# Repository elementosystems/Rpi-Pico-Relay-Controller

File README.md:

# Rpi-Pico-Relay-Controller
IO control board for remote Lab Environment

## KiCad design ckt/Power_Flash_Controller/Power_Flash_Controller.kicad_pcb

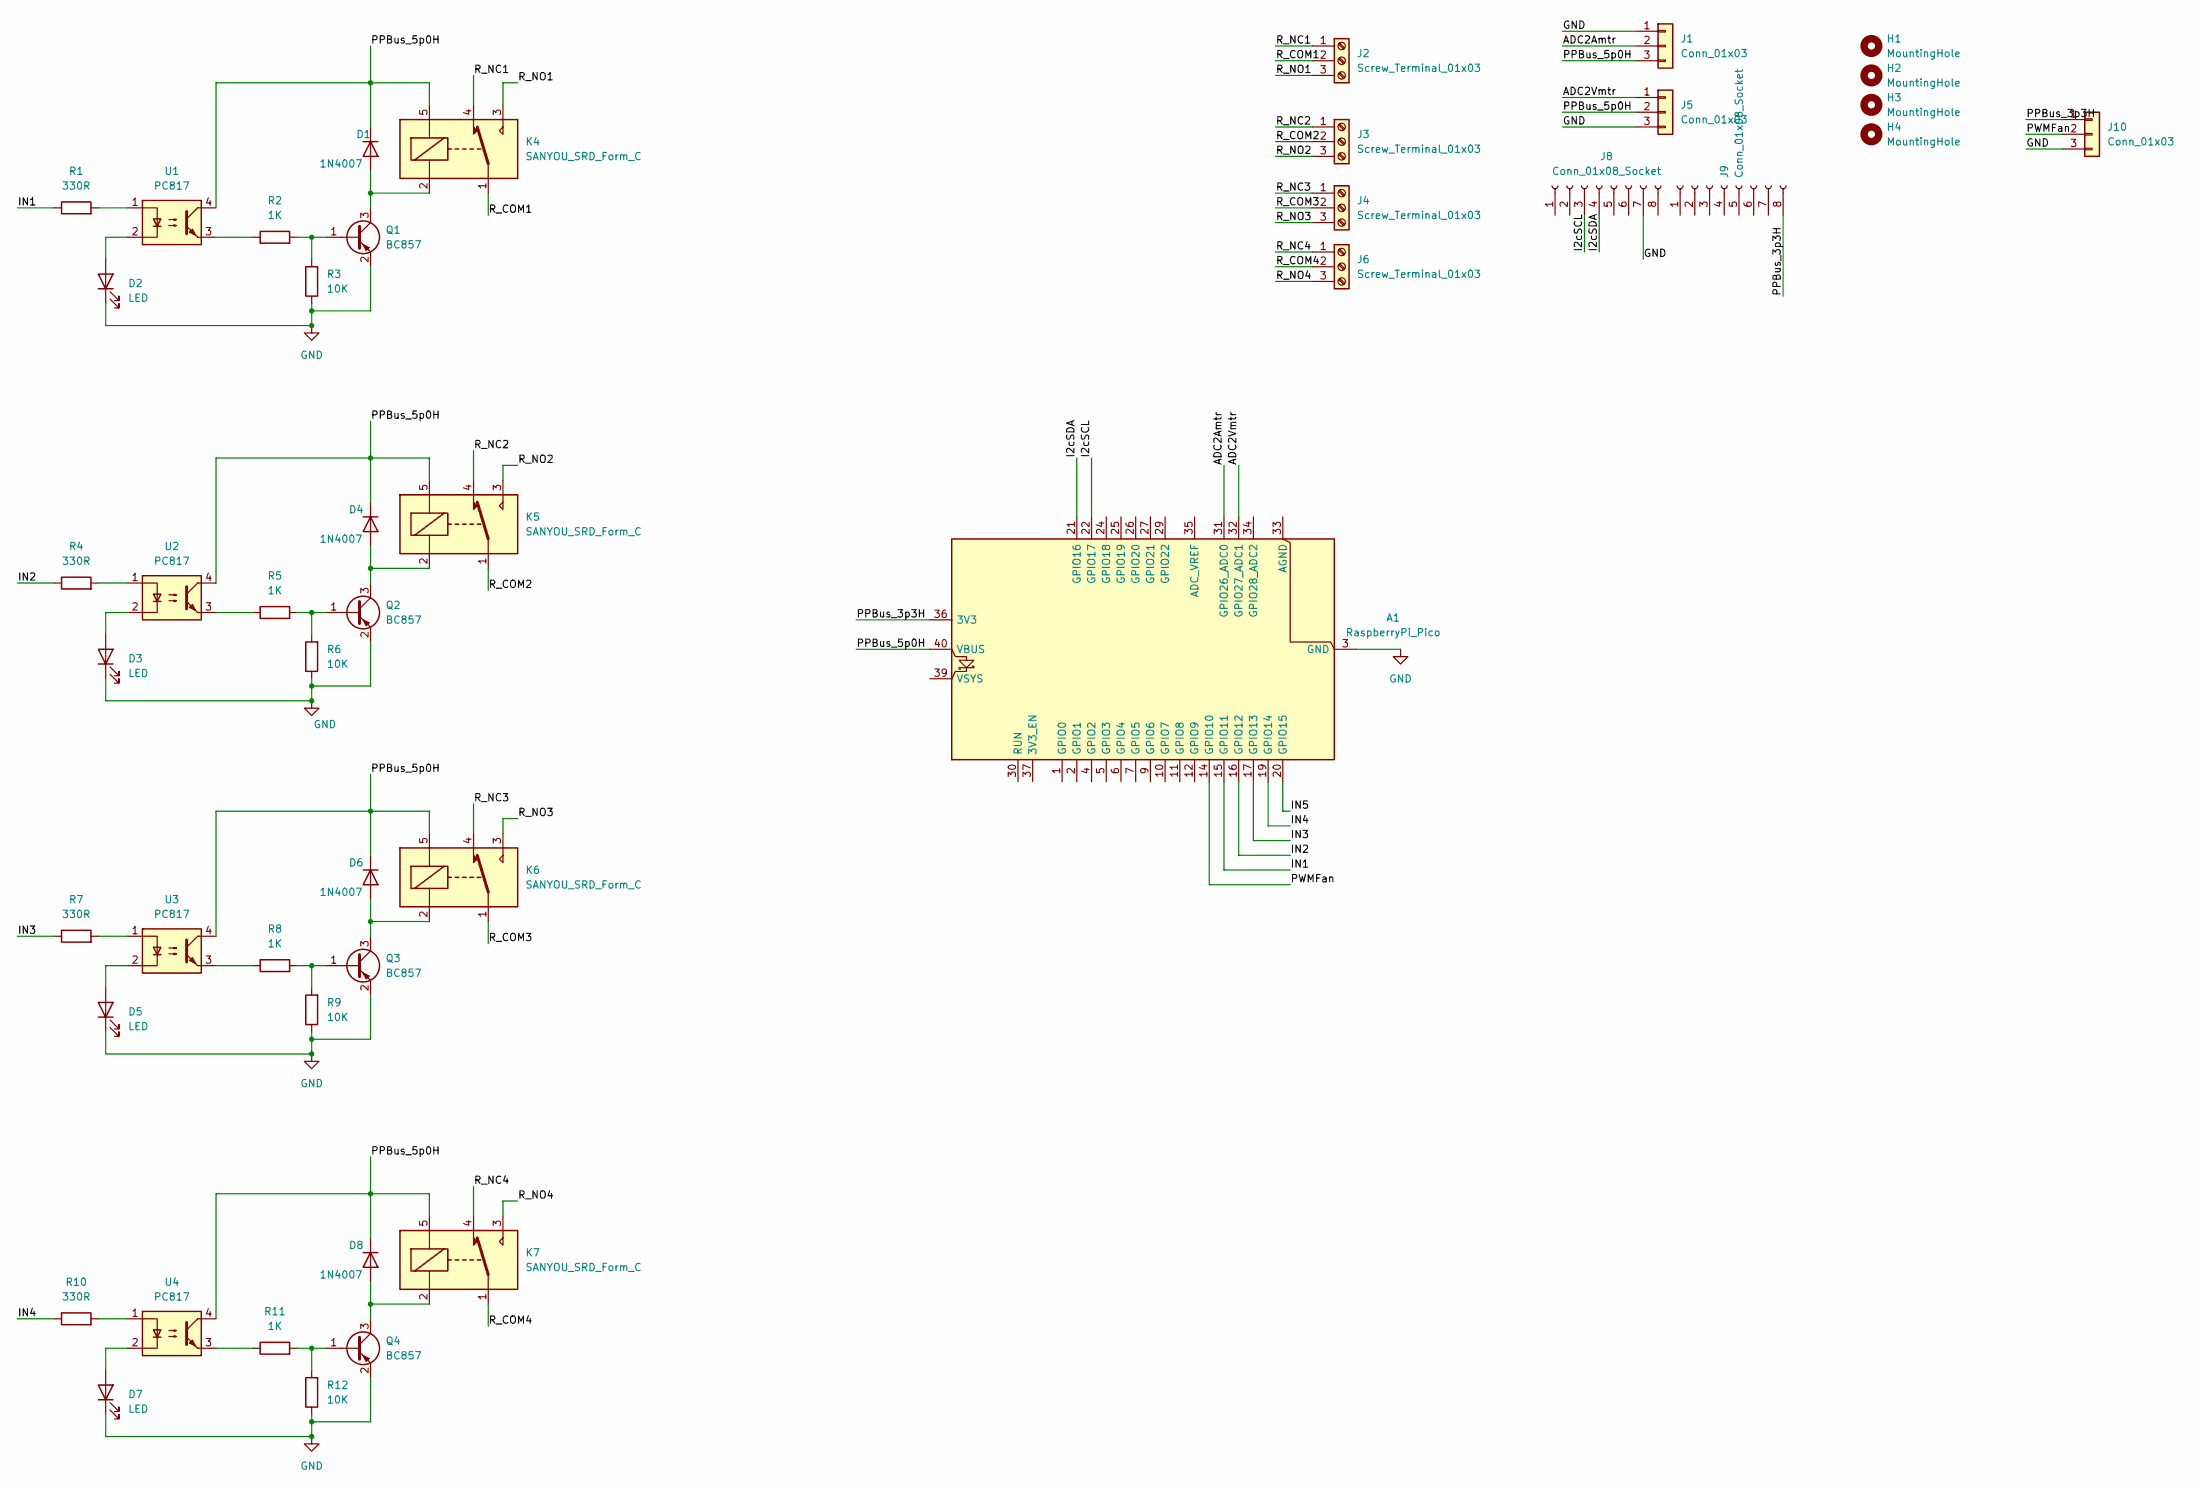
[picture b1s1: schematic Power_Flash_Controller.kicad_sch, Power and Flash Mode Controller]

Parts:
A1: RaspberryPi_Pico; RaspberryPi_Pico_Common_Unspecified
D1, D4, D6, D8: 1N4007; D_DO-41_SOD81_P10.16mm_Horizontal
D2, D3, D5, D7: LED; LED_D3.0mm_IRBlack
H1, H2, H3, H4: MountingHole; MountingHole_2.2mm_M2_DIN965_Pad_TopOnly
J1, J5, J10: Conn_01x03; PinHeader_1x03_P2.54mm_Vertical
J2, J3, J4, J6: Screw_Terminal_01x03; TerminalBlock_MaiXu_MX126-5.0-03P_1x03_P5.00mm
J8, J9: Conn_01x08_Socket; PinHeader_1x08_P2.54mm_Vertical
K4, K5, K6, K7: SANYOU_SRD_Form_C; Relay_SPDT_SANYOU_SRD_Series_Form_C
Q1, Q2, Q3, Q4: BC857; SOT-23
R1, R4, R7, R10: 330R; R_Axial_DIN0204_L3.6mm_D1.6mm_P7.62mm_Horizontal
R2, R5, R8, R11: 1K; R_Axial_DIN0204_L3.6mm_D1.6mm_P7.62mm_Horizontal
R3, R6, R9, R12: 10K; R_Axial_DIN0204_L3.6mm_D1.6mm_P7.62mm_Horizontal
U1, U2, U3, U4: PC817; DIP-4_W7.62mm

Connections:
/ADC2Amtr: A1.31 (GPIO26_ADC0), J1.2
/ADC2Vmtr: A1.32 (GPIO27_ADC1), J5.1
/I2cSCL: A1.22 (GPIO17), J8.3
/I2cSDA: A1.21 (GPIO16), J8.4
/IN1: A1.15 (GPIO11), R1.1
/IN2: A1.16 (GPIO12), R4.1
/IN3: A1.17 (GPIO13), R7.1
/IN4: A1.19 (GPIO14), R10.1
/IN5: A1.20 (GPIO15)
/PPBus_3p3H: A1.36 (3V3), J9.8, J10.1
/PPBus_5p0H: A1.40 (VBUS), D1.1 (K), D4.1 (K), D6.1 (K), D8.1 (K), J1.3, J5.2, K4.5, K5.5, K6.5, K7.5, U1.4, U2.4, U3.4, U4.4
/PWMFan: A1.14 (GPIO10), J10.2
/R_COM1: J2.2, K4.1
/R_COM2: J3.2, K5.1
/R_COM3: J4.2, K6.1
/R_COM4: J6.2, K7.1
/R_NC1: J2.1, K4.4
/R_NC2: J3.1, K5.4
/R_NC3: J4.1, K6.4
/R_NC4: J6.1, K7.4
/R_NO1: J2.3, K4.3
/R_NO2: J3.3, K5.3
/R_NO3: J4.3, K6.3
/R_NO4: J6.3, K7.3
GND: A1.3 (GND), A1.8 (GND), A1.13 (GND), A1.18 (GND), A1.23 (GND), A1.28 (GND), A1.38 (GND), D2.1 (K), D3.1 (K), D5.1 (K), D7.1 (K), J1.1, J5.3, J8.7, J10.3, Q1.2 (E), Q2.2 (E), Q3.2 (E), Q4.2 (E), R3.1, R6.1, R9.1, R12.1
unnamed: D1.2 (A), K4.2, Q1.3 (C)
unnamed: D2.2 (A), U1.2
unnamed: D3.2 (A), U2.2
unnamed: D4.2 (A), K5.2, Q2.3 (C)
unnamed: D5.2 (A), U3.2
unnamed: D6.2 (A), K6.2, Q3.3 (C)
unnamed: D7.2 (A), U4.2
unnamed: D8.2 (A), K7.2, Q4.3 (C)
unnamed: Q1.1 (B), R2.2, R3.2
unnamed: Q2.1 (B), R5.2, R6.2
unnamed: Q3.1 (B), R8.2, R9.2
unnamed: Q4.1 (B), R11.2, R12.2
unnamed: R1.2, U1.1
unnamed: R2.1, U1.3
unnamed: R4.2, U2.1
unnamed: R5.1, U2.3
unnamed: R7.2, U3.1
unnamed: R8.1, U3.3
unnamed: R10.2, U4.1
unnamed: R11.1, U4.3

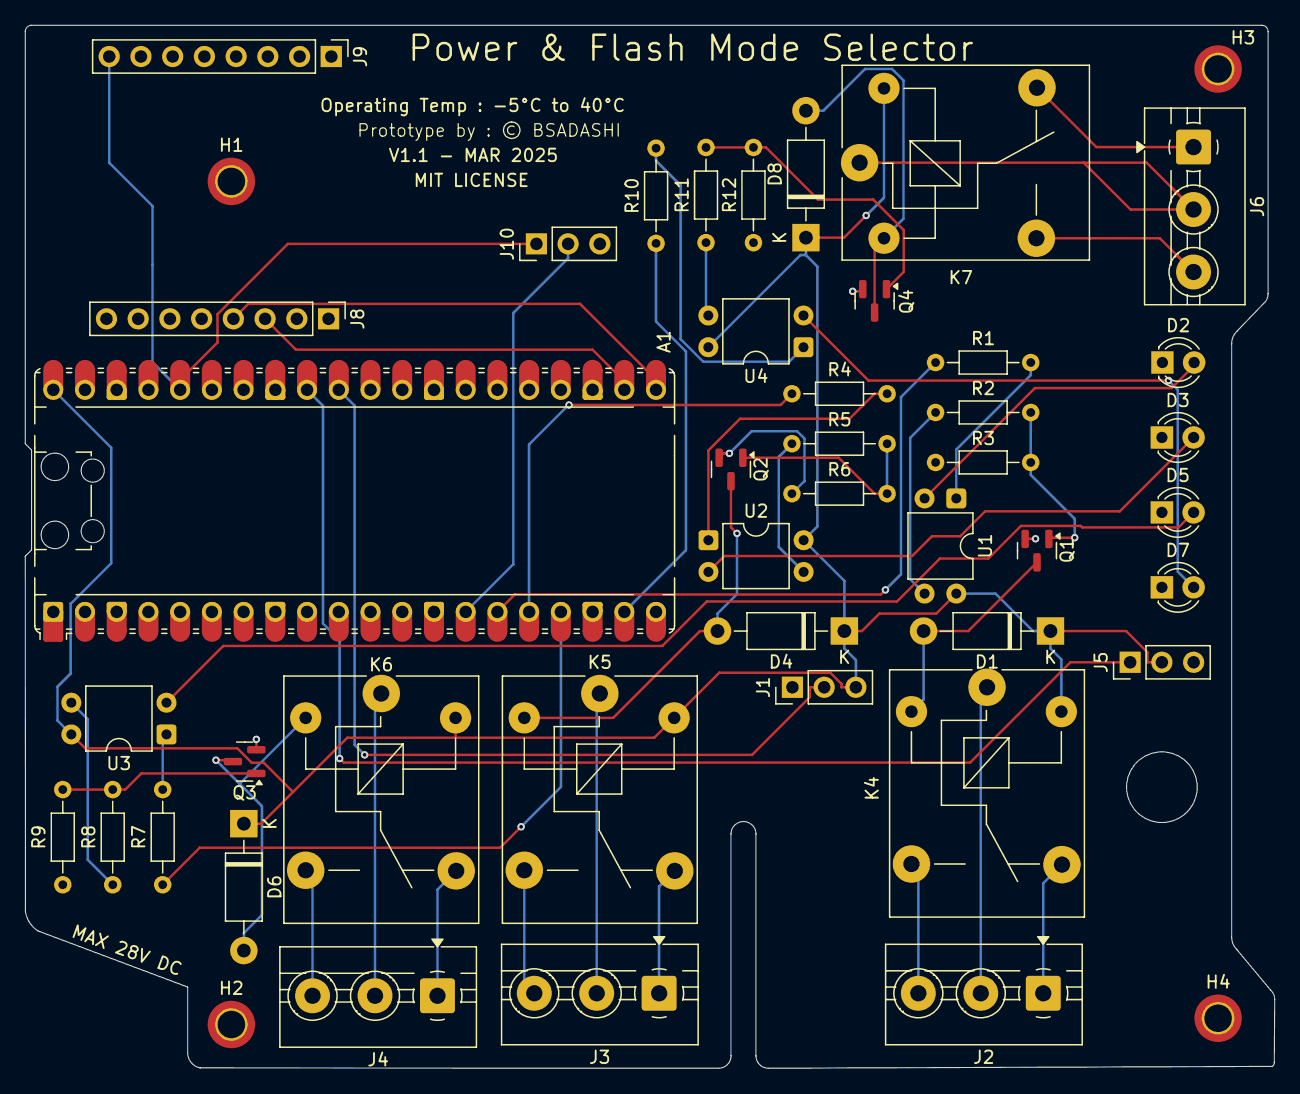
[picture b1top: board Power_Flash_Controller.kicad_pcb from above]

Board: 2 copper layers, 100.0 x 83.5 mm, 46 parts (0 on the bottom side), 44 nets.

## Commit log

2025-02-23 Prototype version, 3 Relay circuits and Pico controller added
2025-02-23 Added 2.1mm Screw holes for mounting and added divet in PCB for microusb port
2025-02-23 Added M2 holes for mounting and updated board design
2025-02-23 gitignore file for KiCad project
2025-02-23 Fixed DRC warnings
2025-02-24 rounded the paths and added GND fill layer
2025-03-03 Update LICENSE
2025-03-11 Added connections for Ammeter and Voltmeter
2025-03-14 added relay no.4 and oled display mount, option for pwm fan and ammeter, voltmeter

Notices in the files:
ckt/Power_Flash_Controller/Power_Flash_Controller.kicad_pcb:
MIT LICENSE
Prototype by : © BSADASHI
